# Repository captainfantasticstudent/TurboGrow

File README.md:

# TurboGrow
System kontroli warunków wzrostu i rozwoju roślin. Układ ma za zadanie w sposób ciągły monitorować stan środowiska w którym rozwija się roślina i reagować  na wszelanie nieporządane zmiany

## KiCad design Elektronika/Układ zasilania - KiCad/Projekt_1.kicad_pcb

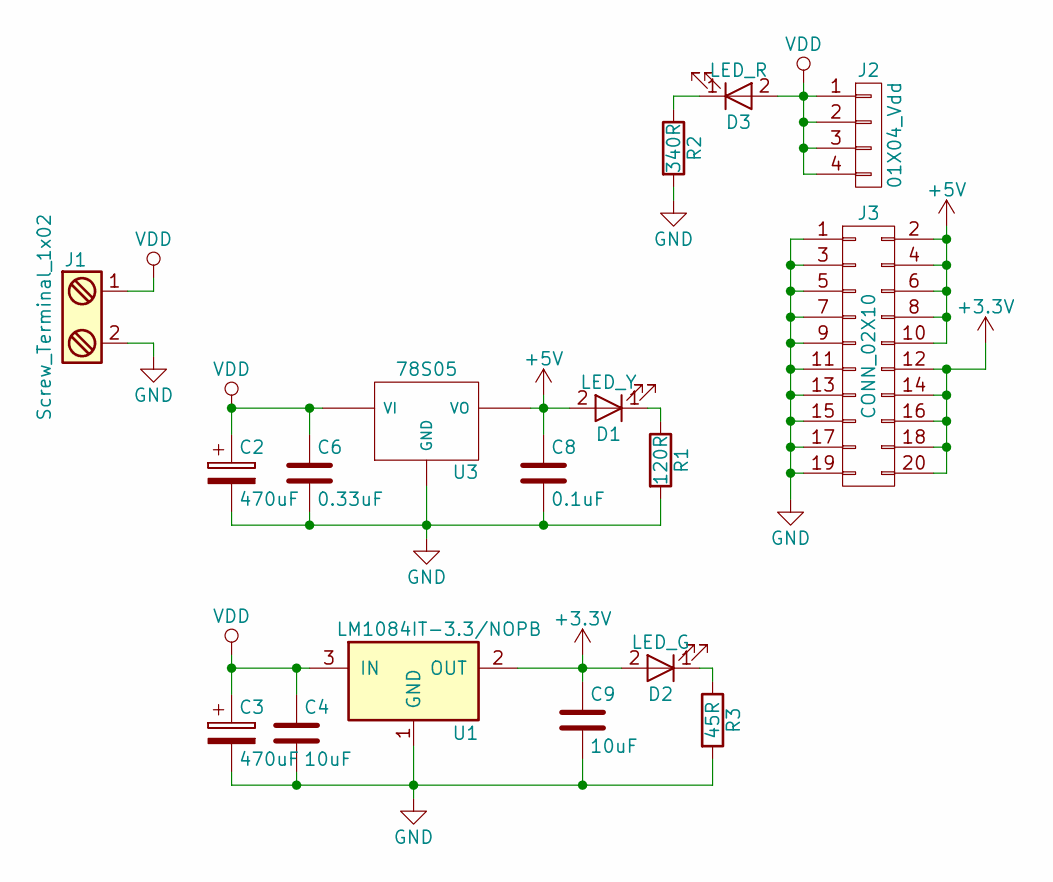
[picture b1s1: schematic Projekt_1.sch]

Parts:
C2, C3: 470uF; CP_Radial_D8.0mm_P2.50mm
C4, C9: 10uF; C_Disc_D3.4mm_W2.1mm_P2.50mm
C6: 0.33uF; C_Disc_D3.4mm_W2.1mm_P2.50mm
C8: 0.1uF; C_Disc_D3.4mm_W2.1mm_P2.50mm
D1: LED_Y; LED_D5.0mm
D2: LED_G; LED_D5.0mm
D3: LED_R; LED_D5.0mm
J1: Screw_Terminal_1x02; TerminalBlock_Pheonix_MKDS1.5-2pol
J2: 01X04_Vdd; Pin_Header_Straight_1x04_Pitch2.54mm
J3: CONN_02X10; Pin_Header_Straight_2x10_Pitch2.54mm
R1: 120R; R_Axial_DIN0207_L6.3mm_D2.5mm_P10.16mm_Horizontal
R2: 340R; R_Axial_DIN0207_L6.3mm_D2.5mm_P10.16mm_Horizontal
R3: 45R; R_Axial_DIN0207_L6.3mm_D2.5mm_P10.16mm_Horizontal
U1: LM1084IT-3.3/NOPB; TO-220_Vertical
U3: 78S05; TO-220_Vertical

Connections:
+3V3: C9.1, D2.2 (A), J3.12, J3.14, J3.16, J3.18, J3.20, U1.2 (OUT)
+5V: C8.1, D1.2 (A), J3.2, J3.4, J3.6, J3.8, J3.10, U3.3 (VO)
GND: C2.2, C3.2, C4.2, C6.2, C8.2, C9.2, J1.2, J3.1, J3.3, J3.5, J3.7, J3.9, J3.11, J3.13, J3.15, J3.17, J3.19, R1.2, R2.2, R3.2, U1.1 (GND), U3.2 (GND)
unnamed: D1.1 (K), R1.1
unnamed: D2.1 (K), R3.1
unnamed: D3.1 (K), R2.1
VDD: C2.1, C3.1, C4.1, C6.1, D3.2 (A), J1.1, J2.1, J2.2, J2.3, J2.4, U1.3 (IN), U3.1 (VI)

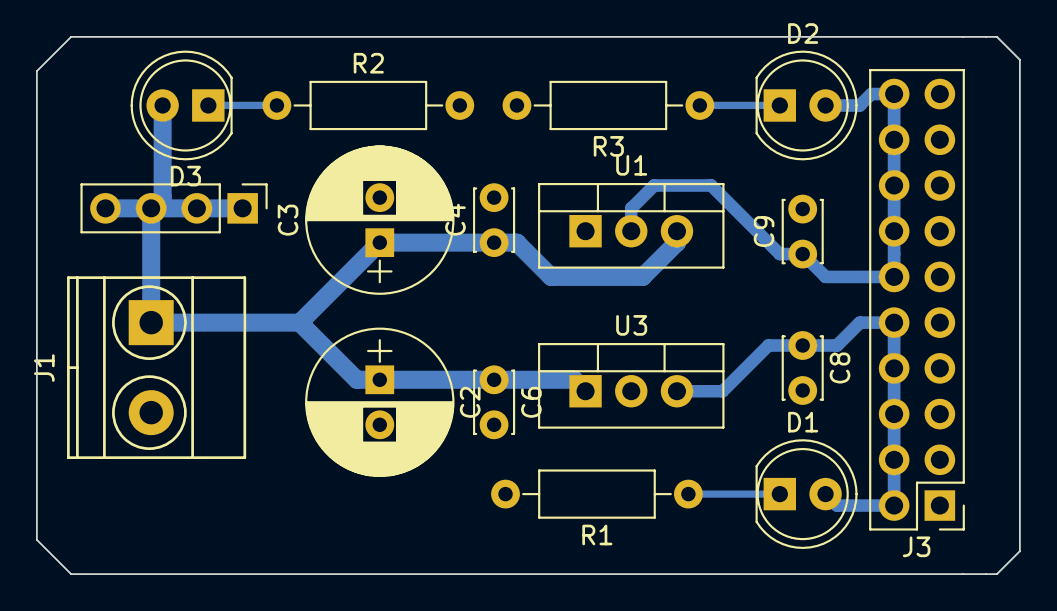
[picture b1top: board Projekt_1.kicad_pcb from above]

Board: 2 copper layers, 54.6 x 29.8 mm, 17 parts (0 on the bottom side), 7 nets.

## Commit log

2017-03-13 Aktualizacja README
2017-03-25 Program dla mikrokontrolera
    Obsługa podstawowych potrzebnych w projekcie peryferiów
2017-03-25 Lekkie zmiany w organizacji plików
2017-03-25 Szybkie zmiany
